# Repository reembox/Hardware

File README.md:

Hardware
========

This repository contains pcb layout files for the reembox project.

The layout files can be opened with [EAGLE](http://www.cadsoft.de/download-eagle/) version 6.4.0 or higher. Since the board fits on a half eurocard, you can use EAGLE in the freeware version without buying a licence.

Check out the [Wiki documentation](https://github.com/reembox/Hardware/wiki) for setting it up.

This project "reembox" © 2013 Jonas Eickhoff is licensed under the Creative Commons Attribution-ShareAlike 3.0 Unported License: http://creativecommons.org/licenses/by-sa/3.0/

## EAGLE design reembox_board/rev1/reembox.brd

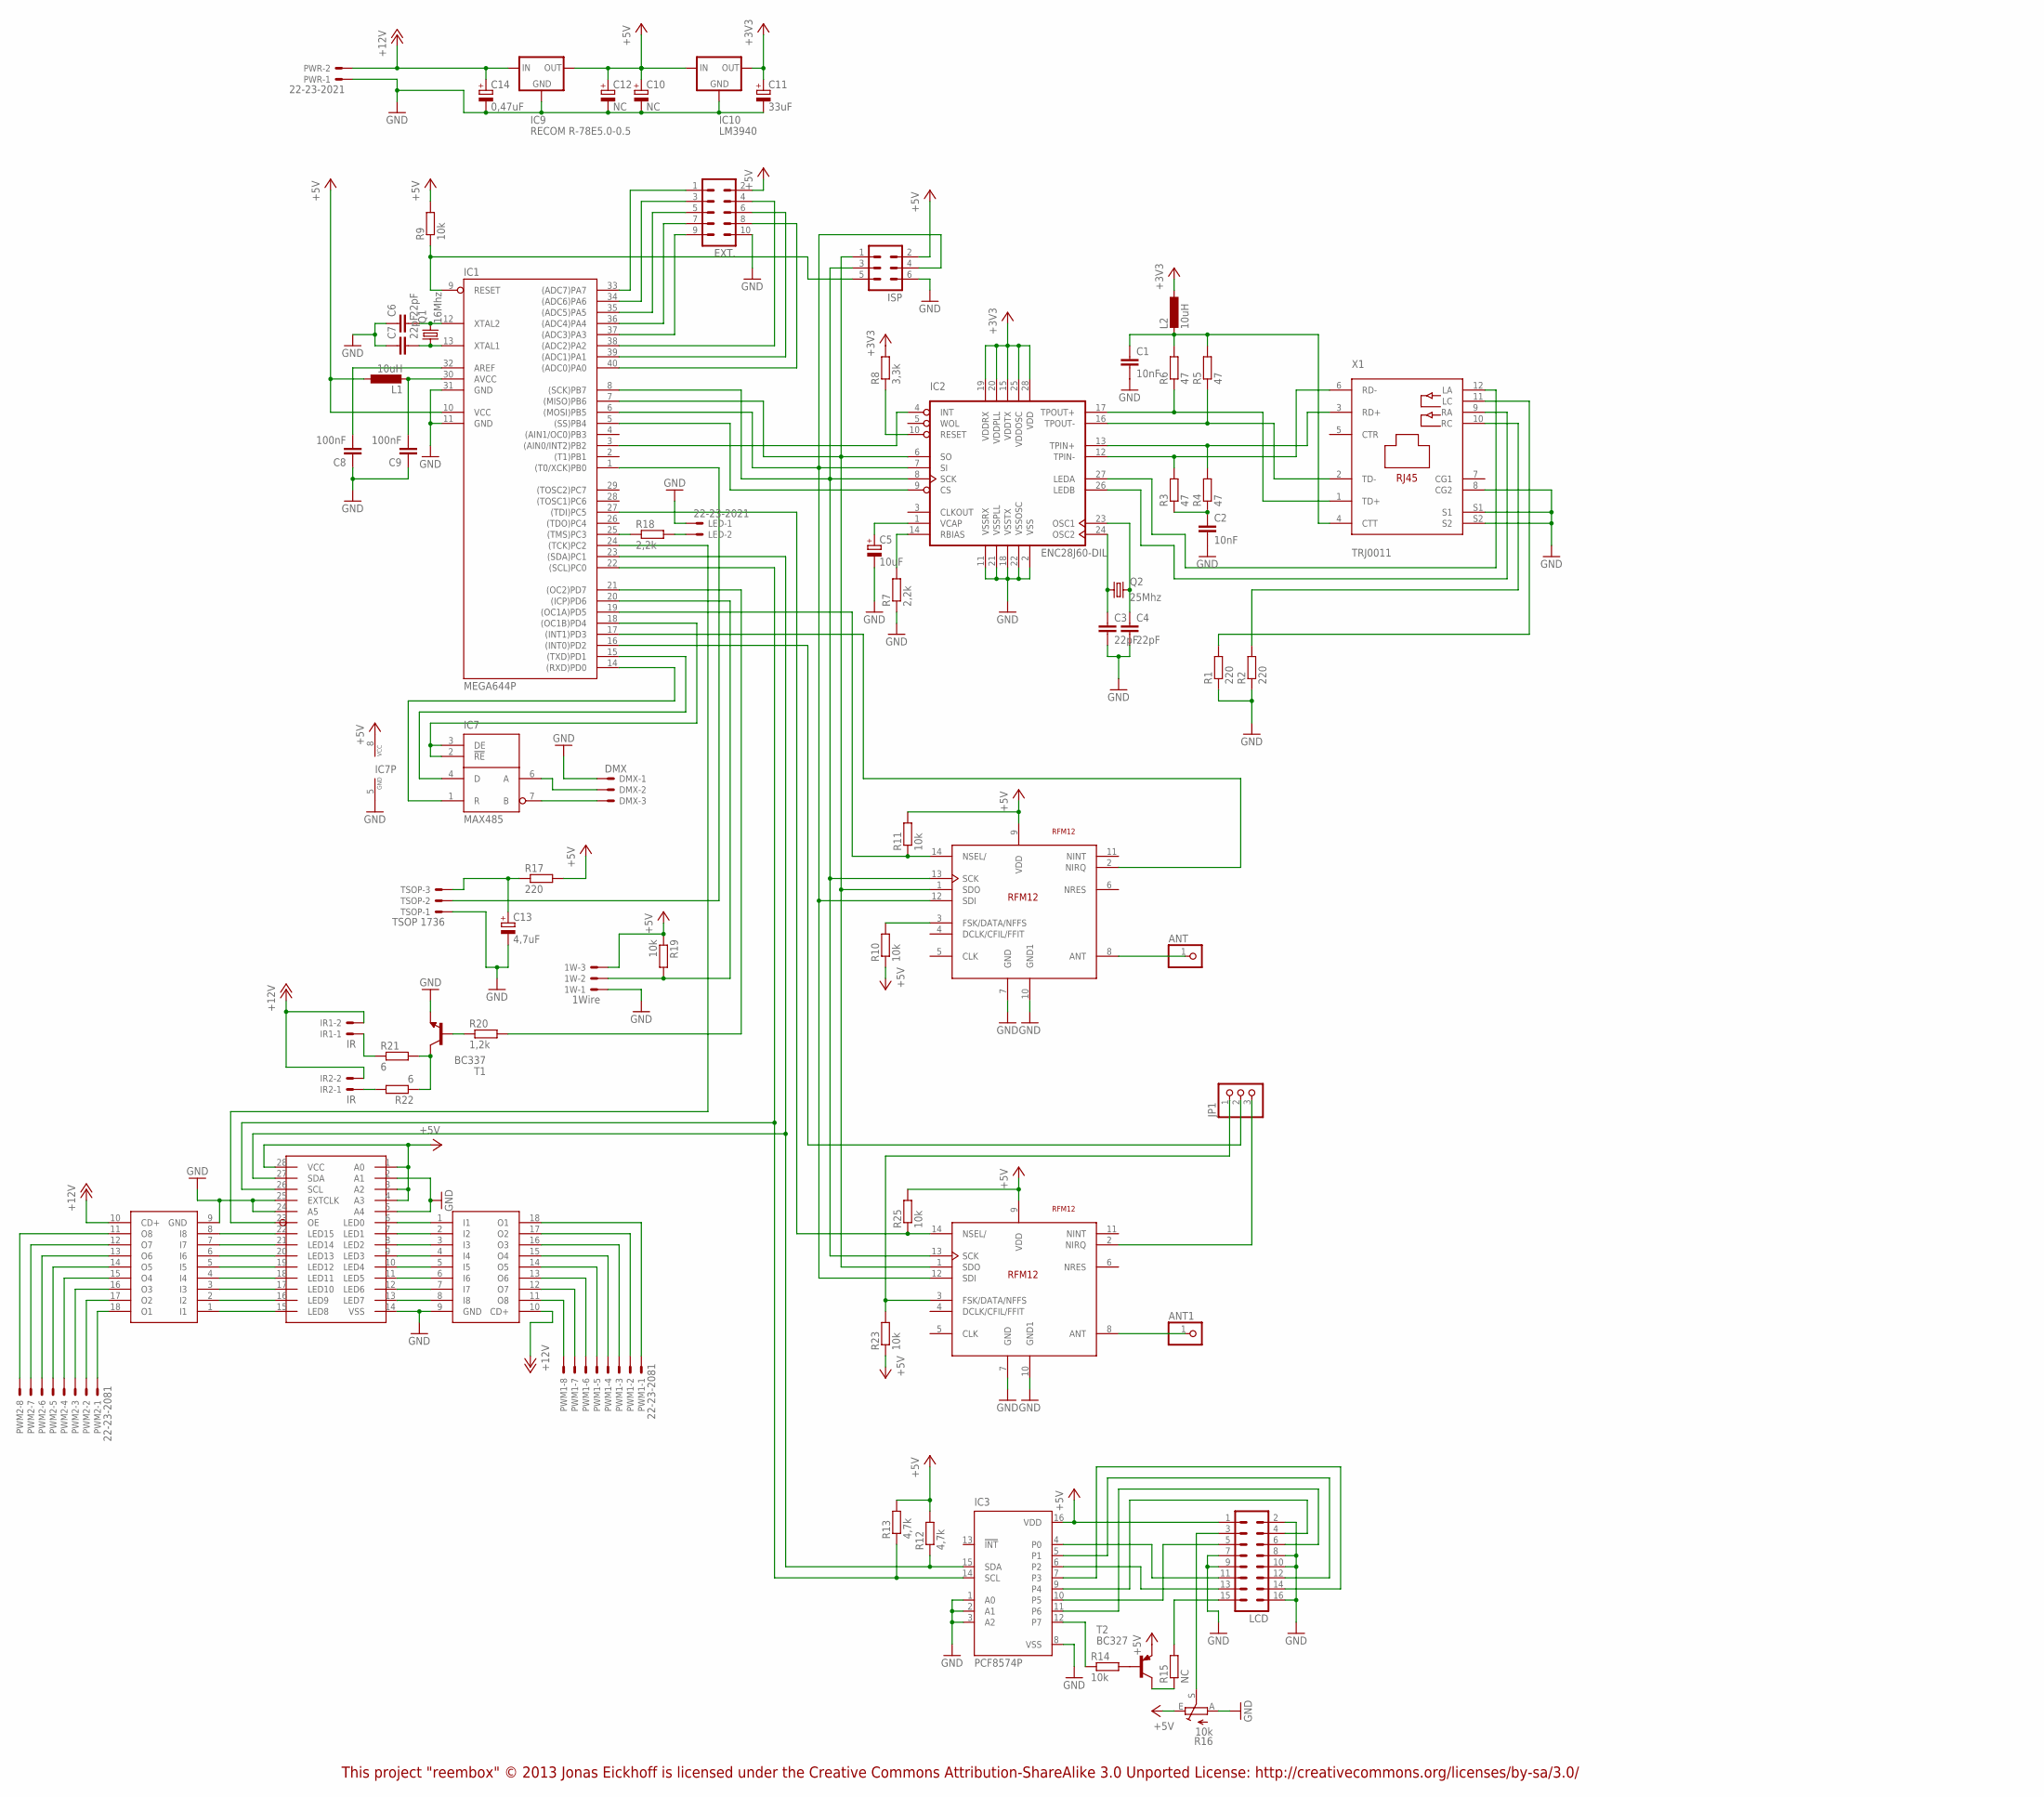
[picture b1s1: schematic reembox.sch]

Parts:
1W: 1Wire; CON-MOLEX_22-23-2031
ANT, ANT1: PINHD-1X1; 1X01
C1, C2: 10nF; C050-025X075
C3, C4, C6, C7: 22pF; C050-024X044
C5: 10uF; E2,5-6
C8, C9: 100nF; C050-025X075
C10, C12: NC; E2,5-6
C11: 33uF; E2,5-6
C13: 4,7uF; E2,5-6E
C14: 0,47uF; E2,5-6
DMX: DMX; 22-23-2031
EXT.: ML10L
IC1: MEGA644P; DIL40
IC2: ENC28J60-DIL; DIL28-3
IC3: PCF8574P; DIL16
IC4: PCA9685PW; TSSOP28
IC5, IC6: ULN2803; DIL18
IC7: MAX485; DIL08
IC8, IC11: RFM12
IC9: RECOM R-78E5.0-0.5; 78XXS
IC10: LM3940; 78XXS
IR1: IR; 22-23-2021
IR2: IR; 22-23-2021; MPN 22-23-2021
ISP: ML6
JP1: PINHD-1X3; 1X03
L1, L2: 10uH; 0207/2V
LCD: ML16
LED: 22-23-2021; MPN 22-23-2021
PWM1, PWM2: 22-23-2081
PWR: 22-23-2021
Q1: 16Mhz; HC49U-V
Q2: 25Mhz; HC49U-V
R1, R2, R17: 220; 0207/2V
R3, R4, R5, R6: 47; 0207/2V
R7: 2,2k; 0207/7
R8: 3,3k; 0207/10
R9, R25: 10k; 0207/2V
R10, R11, R14, R19, R23: 10k; 0207/10
R12, R13: 4,7k; 0207/10
R15: NC; 0207/10
R16: 10k; PT-10S
R18: 2,2k; 0207/2V
R20: 1,2k; RCL_0207/2V
R21, R22: 6; RCL_0207/2V
T1: BC337; TO92
T2: BC327; TO92
TSOP: TSOP 1736; 22-23-2031
X1: TRJ0011

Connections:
+3V3: C11.+, IC2.15 (VDDTX), IC2.19 (VDDRX), IC2.20 (VDDPLL), IC2.25 (VDDOSC), IC2.28 (VDD), IC10.OUT, L2.1, R8.2
+5V: 1W.3, C10.+, C12.+, EXT..2, IC1.10 (VCC), IC3.16 (VDD), IC4.1 (A0), IC4.3 (A2), IC4.4 (A3), IC4.28 (VCC), IC7.8 (VCC), IC8.9 (VDD), IC9.OUT, IC10.IN, IC11.9 (VDD), ISP.2, L1.1, LCD.1, R9.2, R10.1, R11.2, R12.2, R13.2, R16.E, R17.2, R19.1, R23.1, R25.2, T2.1 (E)
+12V: C14.+, IC5.10 (CD+), IC6.10 (CD+), IC9.IN, IR1.2, IR2.2, PWR.2
GND: 1W.1, C1.2, C2.2, C3.2, C4.2, C5.-, C6.1, C7.1, C8.1, C9.1, C10.-, C11.-, C12.-, C13.-, C14.-, DMX.1, EXT..10, IC1.11 (GND), IC1.31 (GND), IC2.2 (VSS), IC2.11 (VSSRX), IC2.18 (VSSTX), IC2.21 (VSSPLL), IC2.22 (VSSOSC), IC3.1 (A0), IC3.2 (A1), IC3.3 (A2), IC3.8 (VSS), IC4.2 (A1), IC4.5 (A4), IC4.14 (VSS), IC4.24 (A5), IC4.25 (EXTCLK), IC5.9 (GND), IC6.9 (GND), IC7.5 (GND), IC8.7 (GND), IC8.10 (GND1), IC9.GND, IC10.GND, IC11.7 (GND), IC11.10 (GND1), ISP.6, LCD.2, LCD.7, LCD.8, LCD.9, LCD.10, LCD.16, LED.1, PWR.1, R1.1, R2.1, R7.1, R16.A, T1.1 (E), TSOP.1, X1.8 (CG2), X1.S1, X1.S2
LED: IC1.1 ((T0/XCK)PB0), TSOP.2
unnamed: IC2.17 (TPOUT+), R6.1, X1.1 (TD+)
unnamed: IC2.16 (TPOUT-), R5.1, X1.2 (TD-)
unnamed: IC2.13 (TPIN+), R4.2, X1.3 (RD+)
unnamed: IC2.12 (TPIN-), R3.2, X1.6 (RD-)
unnamed: IC2.27 (LEDA), X1.12 (LA)
unnamed: IC2.26 (LEDB), X1.9 (RA)
unnamed: R2.2, X1.10 (RC)
unnamed: R1.2, X1.11 (LC)
unnamed: C2.1, R3.1, R4.1
unnamed: C3.1, IC2.24 (OSC2), Q2.1
unnamed: C4.1, IC2.23 (OSC1), Q2.2
unnamed: C1.1, L2.2, R5.2, R6.2, X1.4 (CTT)
unnamed: IC2.10 (RESET), R8.1
unnamed: IC2.14 (RBIAS), R7.2
unnamed: C5.+, IC2.1 (VCAP)
unnamed: C6.2, IC1.12 (XTAL2), Q1.2
unnamed: C7.2, IC1.13 (XTAL1), Q1.1
unnamed: IC1.5 ((SS)PB4), IC2.9 (CS)
unnamed: IC1.17 ((INT1)PD3), IC8.2 (NIRQ)
unnamed: IC1.27 ((TDI)PC5), IC11.14 (NSEL/), R25.1
unnamed: IC1.16 ((INT0)PD2), JP1.2
unnamed: C8.2, IC1.32 (AREF)
unnamed: IC1.3 ((AIN0/INT2)PB2), IC2.4 (INT)
unnamed: IC1.9 (RESET), ISP.5, R9.1
unnamed: IC1.19 ((OC1A)PD5), IC8.14 (NSEL/), R11.1
unnamed: C9.2, IC1.30 (AVCC), L1.2
unnamed: DMX.2, IC7.6 (A)
unnamed: IC1.18 ((OC1B)PD4), IC7.2 (!RE), IC7.3 (DE)
unnamed: DMX.3, IC7.7 (B)
unnamed: IC1.15 ((TXD)PD1), IC7.4 (D)
unnamed: IC1.14 ((RXD)PD0), IC7.1 (R)
unnamed: IC1.23 ((SDA)PC1), IC3.15 (SDA), IC4.27 (SDA), R12.1
unnamed: IC1.22 ((SCL)PC0), IC3.14 (SCL), IC4.26 (SCL), R13.1
unnamed: IC3.12 (P7), R14.1
unnamed: R14.2, T2.2 (B)
unnamed: R15.1, T2.3 (C)
unnamed: LCD.15, R15.2
unnamed: IC3.4 (P0), LCD.11
unnamed: IC3.5 (P1), LCD.12
unnamed: IC3.6 (P2), LCD.13
unnamed: IC3.7 (P3), LCD.14
unnamed: IC3.9 (P4), LCD.4
unnamed: IC3.10 (P5), LCD.5
unnamed: IC3.11 (P6), LCD.6
unnamed: ANT.1, IC8.8 (ANT)
unnamed: IC1.24 ((TCK)PC2), IC4.23 (OE)
unnamed: LCD.3, R16.S
unnamed: C13.+, R17.1, TSOP.3
unnamed: IC4.15 (LED8), IC5.1 (I1)
unnamed: IC1.21 ((OC2)PD7), R20.2
unnamed: IC1.8 ((SCK)PB7), IC2.8 (SCK), IC8.13 (SCK), IC11.13 (SCK), ISP.3
unnamed: 1W.2, IC1.20 ((ICP)PD6), R19.2
unnamed: R20.1, T1.2 (B)
unnamed: IC4.16 (LED9), IC5.2 (I2)
unnamed: R21.2, R22.1, T1.3 (C)
unnamed: IR1.1, R21.1
unnamed: IC4.17 (LED10), IC5.3 (I3)
unnamed: IC4.18 (LED11), IC5.4 (I4)
unnamed: IC4.19 (LED12), IC5.5 (I5)
unnamed: IC4.20 (LED13), IC5.6 (I6)
unnamed: IC4.21 (LED14), IC5.7 (I7)
unnamed: IC4.22 (LED15), IC5.8 (I8)
unnamed: IC4.6 (LED0), IC6.1 (I1)
unnamed: IC4.8 (LED2), IC6.3 (I3)
unnamed: IC4.7 (LED1), IC6.2 (I2)
unnamed: IC4.10 (LED4), IC6.5 (I5)
unnamed: IC4.9 (LED3), IC6.4 (I4)
unnamed: IC4.12 (LED6), IC6.7 (I7)
unnamed: IC4.11 (LED5), IC6.6 (I6)
unnamed: IC4.13 (LED7), IC6.8 (I8)
unnamed: IC6.13 (O6), PWM1.6
unnamed: IC6.17 (O2), PWM1.2
unnamed: IC5.18 (O1), PWM2.1
unnamed: IC5.17 (O2), PWM2.2
unnamed: IC5.16 (O3), PWM2.3
unnamed: IC5.15 (O4), PWM2.4
unnamed: IC5.14 (O5), PWM2.5
unnamed: IC5.13 (O6), PWM2.6
unnamed: IC5.12 (O7), PWM2.7
unnamed: IC5.11 (O8), PWM2.8
unnamed: IC6.11 (O8), PWM1.8
unnamed: IC6.12 (O7), PWM1.7
unnamed: IC6.14 (O5), PWM1.5
unnamed: IC6.15 (O4), PWM1.4
unnamed: IC6.16 (O3), PWM1.3
unnamed: IC6.18 (O1), PWM1.1
unnamed: IC1.25 ((TMS)PC3), R18.1
unnamed: EXT..1, IC1.33 ((ADC7)PA7)
unnamed: EXT..3, IC1.34 ((ADC6)PA6)
unnamed: EXT..5, IC1.35 ((ADC5)PA5)
unnamed: EXT..7, IC1.36 ((ADC4)PA4)
unnamed: EXT..9, IC1.37 ((ADC3)PA3)
unnamed: EXT..4, IC1.38 ((ADC2)PA2)
unnamed: EXT..6, IC1.39 ((ADC1)PA1)
unnamed: EXT..8, IC1.40 ((ADC0)PA0)
unnamed: IC1.6 ((MOSI)PB5), IC2.7 (SI), IC8.12 (SDI), IC11.12 (SDI), ISP.4
unnamed: LED.2, R18.2
unnamed: IR2.1, R22.2
unnamed: IC1.7 ((MISO)PB6), IC2.6 (SO), IC8.1 (SDO), IC11.1 (SDO), ISP.1
unnamed: IC11.3 (FSK/DATA/NFFS), JP1.1, R23.2
unnamed: IC11.2 (NIRQ), JP1.3
unnamed: ANT1.1, IC11.8 (ANT)
unnamed: IC8.3 (FSK/DATA/NFFS), R10.2

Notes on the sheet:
This project "reembox" © 2013 Jonas Eickhoff is licensed under the Creative Commons Attribution-ShareAlike 3.0 Unported License: http://creativecommons.org/licenses/by-sa/3.0/

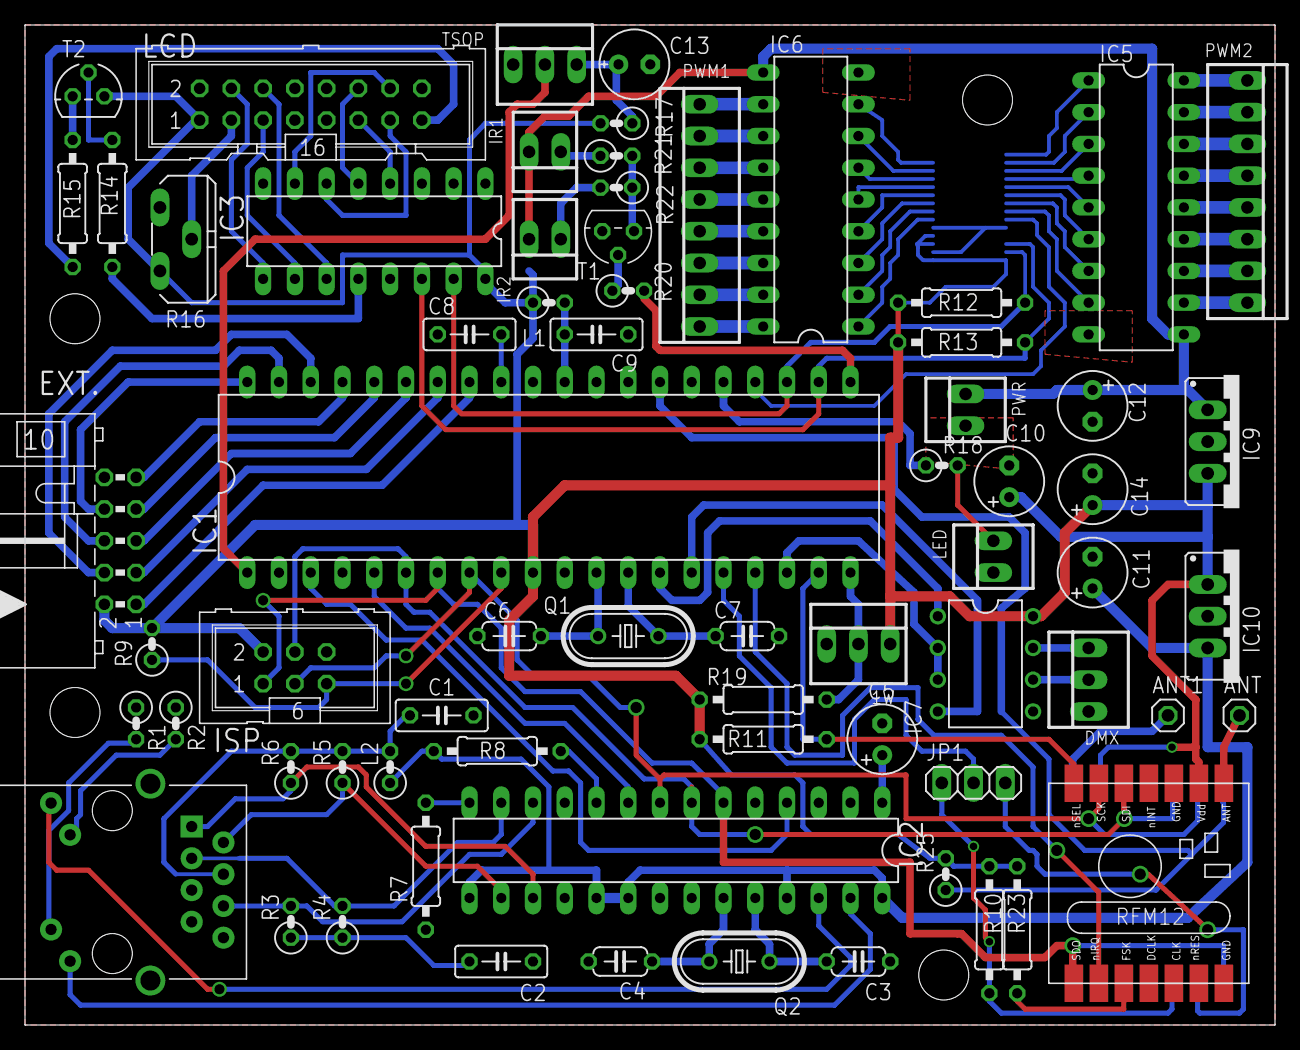
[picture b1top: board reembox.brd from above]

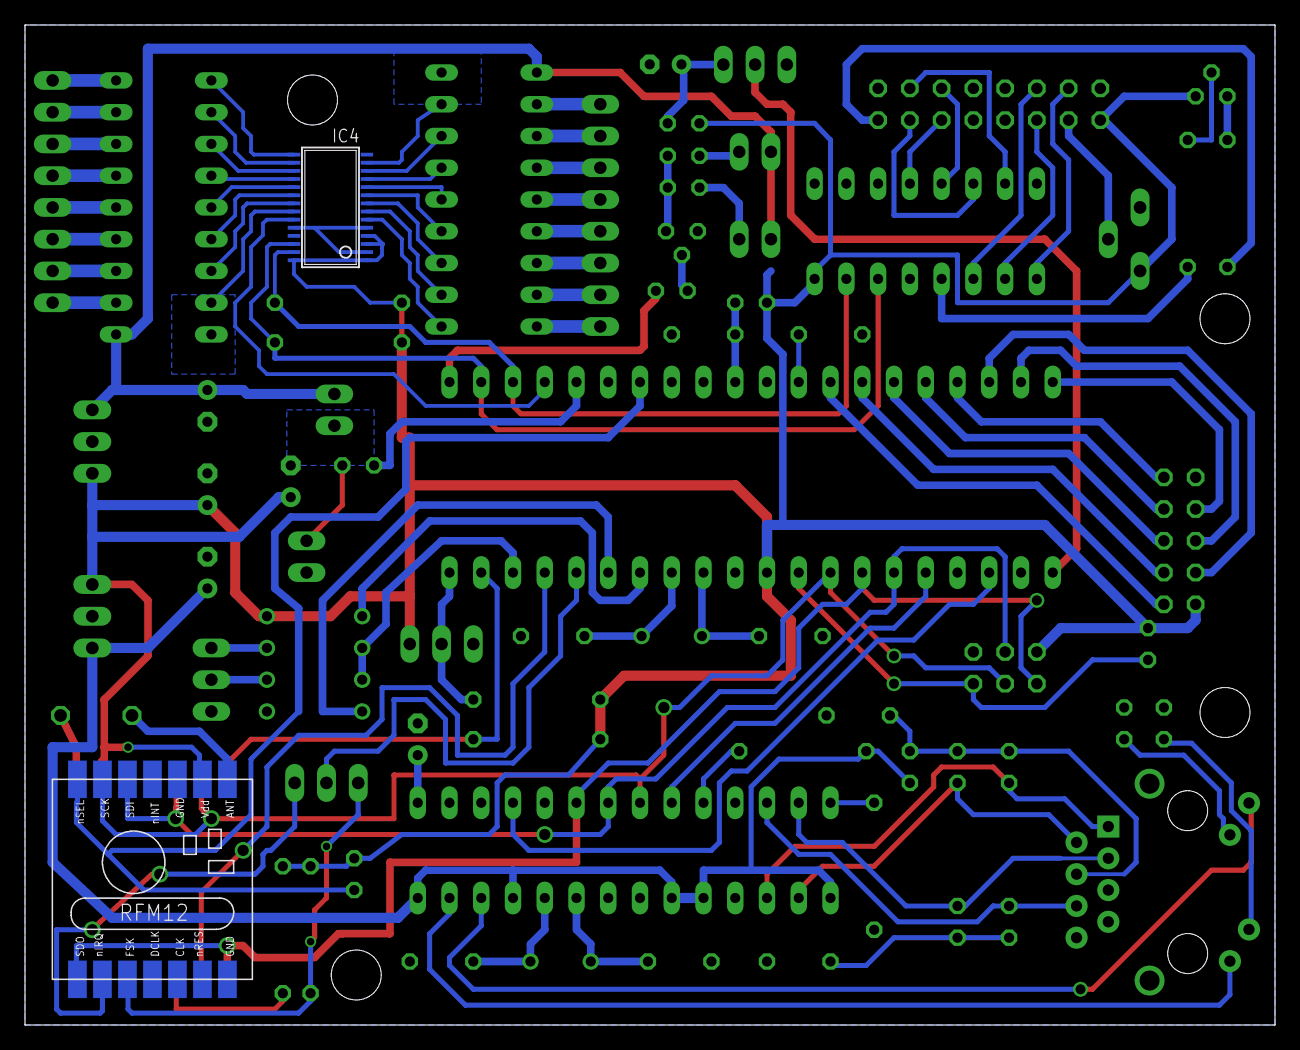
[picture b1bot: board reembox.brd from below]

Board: 2 copper layers, 100.0 x 80.0 mm, 71 parts (2 on the bottom side), 108 nets.

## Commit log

2013-06-17 adding laser cut file for case
2013-07-29 added board
2013-07-29 adding eagle hint
2013-07-29 added LICENSE
2013-08-06 added ethersex config file
2014-11-14 pantries updated + ethersex pinning file

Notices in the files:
reembox_board/rev1/reembox.sch:
The project "reembox" © 2013 Jonas Eickhoff is licensed under the Creative Commons Attribution-ShareAlike 3.0 Unported License: http://creativecommons.org/licenses/by-sa/3.0
